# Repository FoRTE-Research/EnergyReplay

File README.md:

## Overview

This is a hardware system for replaying arbitrary energy harvesting traces to drive experimentation
on batteryless systems. It does so by measuring the voltage at the load and the current across a shunt
resistor to determine instantaneous power input into the load and comparing this actual power input to
a desired time-varying setpoint; if the actual power is below (above) the setpoint, it increases
(decreases) supply voltage produced by a DAC to approach the setpoint. Since this is all done in
software, you are free to implement whatever arbitrary functions may affect the power in your imagined
system - IV curves for a solar panel, voltage-dependent efficiencies for a converter/regulator, etc.

#### Project Status

V1.2 is available as part of this Github repo, but the PCBs have not been ordered. The only difference
between V1.1 and V1.2 is the addition of the voltage divider (R18 and R19) to reduce measured load
voltage. Because V1.1 measures load voltage directly, it cannot produce a load voltage higher than
~3.3V (software will stop voltage from increasing further if load voltage approaches this point to
avoid damaging the hardware).

An assembled and validated PCB for V1.1 is available in the lab.

## Hardware

Schematic and PCB designs are generated in KiCad version 9.

The central microcontroller is an MSP430FR5994, which drives an MCP4725 12-bit DAC. Both the MSP430 and
DAC operate at 3.3V; the output of the DAC is fed into an amplifier to increase its dynamic range to 5V.
Current flows across a 0.5 ohm shunt resistor through an optional diode and into the load. Load current
is measured by taking the voltage across the shunt resistor using a 150x differential amplifier into one
ADC pin of the MSP430. Load voltage is divided by 2 using a resistive voltage divider and fed into
another ADC pin of the MSP430. The short-circuit current of the OPA2837 op amps used is roughly 50 mA,
so at 5V the nominal maximum output power is about 250 mW.

LEDs and switches are available for basic debugging and interactive use.

#### Jumpers

**J1:** Debug header for programming the MSP430FR5994.

**J2:** Power select jumper for replay system. The center pin is connected to the system supply voltage;
it can draw power either from the debug header or from the 3V3 pin on J5.

**J3/J4:** Jumpers to connect and disconnect the green and red LEDs.

**J5:** GPIO breakout header. Also provides access to ground and 3V3 pins for supplying the system from
a non-debugger source.

**J6:** Jumper for optional diode use. RAW is connected to the load side of the shunt resistor and can
be connected to the load if the diode is not desired. Closing this jumper connects the load side of the
shunt resistor to an LM66100 ideal diode to prevent current backflow from the load. When J6 is closed,
the load should be connected on the OUT pin of J7.

**J7:** Jumper providing access to output pin for connecting load and ground pin for convenience. Do not
close this jumper.

## Software

Code is generated as a Code Composer Studio version 11 project.

The energy trace to replay is defined in the [dac.h](Code/dac.h) file as a `const float powerArray[]`
containing the setpoints and a `#define TIMESTEP` macro to set the time (in milliseconds) that power
should stay at each setpoint. This timestep is used to calculate a period value for a hardware timer
that tracks the time spent at each setpoint; when the timer rolls over, the setpoint increments.

The main application loop reads samples from the shunt and load ADC pins, converts those readings to
an actual power measurement, and compares them to the desired setpoint. The output voltage is
incremented/decremented by 1 on each iteration of the main loop; this is basically a PID controller
with K<sub>P</sub> = 1 and K<sub>I</sub> = K<sub>D</sub> = 0. Improving the design of this control
loop is one avenue for improvement in future iterations, although it currently works "well enough".
ADC, timer, and software control are all decoupled - increasing software execution speed (e.g., by
doing the actual power calculation in hardware using some clever op-amp circuits) should only have
the effect of reducing the response time of the control loop and not mess with the timing of the
power trace. If you do significantly increase the software execution speed, you should double check
that the ADC measurements are blocking so that it doesn't overshoot based on stale power readings.

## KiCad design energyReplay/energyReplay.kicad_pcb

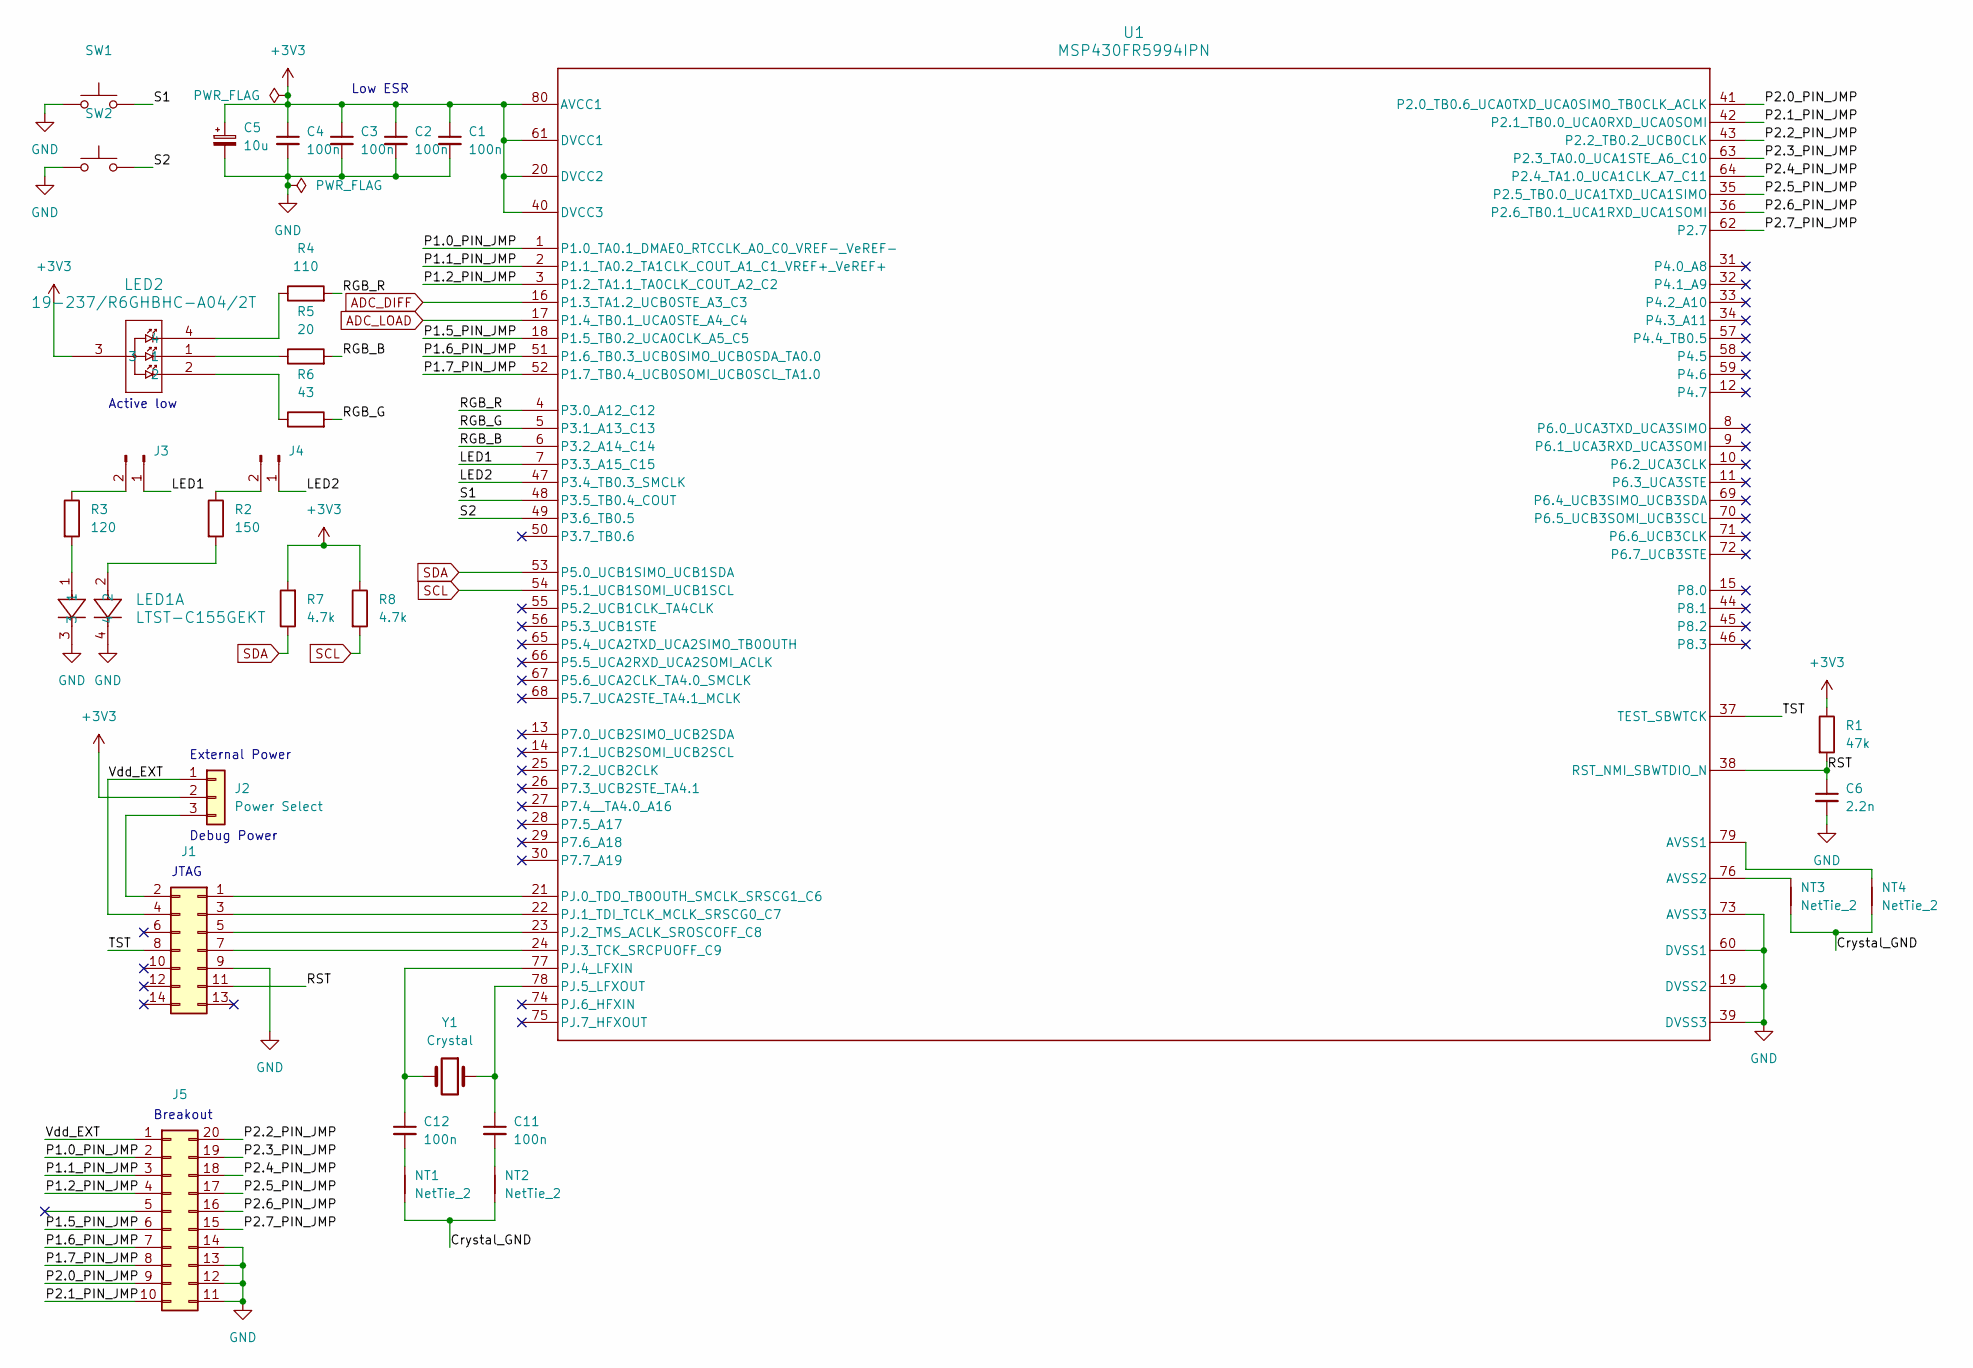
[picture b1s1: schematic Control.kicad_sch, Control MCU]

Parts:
C1, C2, C3, C4, C11, C12: 100n; C_1206_3216Metric
C5: 10u; C_1206_3216Metric
C6: 2.2n; C_1206_3216Metric
J1: Conn_02x07_Odd_Even; PinHeader_2x07_P2.54mm_Vertical
J2: Power Select; PinHeader_1x03_P2.54mm_Vertical
J3, J4: Conn_01x02_Pin; PinHeader_1x02_P2.54mm_Vertical
J5: Conn_02x10_Counter_Clockwise; PinHeader_2x10_P2.54mm_Vertical
LED1: LTST-C155GEKT; DIODE_LTST-C155GEKT_LTO
LED2: 19-237/R6GHBHC-A04/2T; EAST1616RGB_SMD_B_EVE
NT1, NT2, NT3, NT4: NetTie_2; NetTie-2_SMD_Pad0.2mm
R1: 47k; R_1206_3216Metric
R2: 150; R_1206_3216Metric
R3: 120; R_1206_3216Metric
R4: 110; R_1206_3216Metric
R5: 20; R_1206_3216Metric
R6: 43; R_1206_3216Metric
R7, R8: 4.7k; R_1206_3216Metric
SW1, SW2: SW_Push; SW_TL59NF160Q
U1: MSP430FR5994IPN; PN0080A_N
Y1: Crystal; XTAL_MS1V-T1K-32.768KHZ-12.5PF-20PPM-TA-QC

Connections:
+3V3: C1.1, C2.1, C3.1, C4.1, C5.1, J2.2, LED2.3, R1.1, R7.2, R8.1, U1.20 (DVCC2), U1.40 (DVCC3), U1.61 (DVCC1), U1.80 (AVCC1); also elsewhere on the board
/Control/Crystal_GND: NT1.1, NT2.1, NT3.1, NT4.1
/Control/LED1: J3.1, U1.7 (P3.3_A15_C15)
/Control/LED2: J4.1, U1.47 (P3.4_TB0.3_SMCLK)
/Control/P1.0_PIN_JMP: J5.2, U1.1 (P1.0_TA0.1_DMAE0_RTCCLK_A0_C0_VREF-_VeR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)
/Control/P1.1_PIN_JMP: J5.3, U1.2 (P1.1_TA0.2_TA1CLK_COUT_A1_C1_VREF+_VeRE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)
/Control/P1.2_PIN_JMP: J5.4, U1.3 (P1.2_TA1.1_TA0CLK_COUT_A2_C2)
/Control/P1.5_PIN_JMP: J5.6, U1.18 (P1.5_TB0.2_UCA0CLK_A5_C5)
/Control/P1.6_PIN_JMP: J5.7, U1.51 (P1.6_TB0.3_UCB0SIMO_UCB0SDA_TA0.0)
/Control/P1.7_PIN_JMP: J5.8, U1.52 (P1.7_TB0.4_UCB0SOMI_UCB0SCL_TA1.0)
/Control/P2.0_PIN_JMP: J5.9, U1.41 (P2.0_TB0.6_UCA0TXD_UCA0SIMO_TB0CLK_ACLK)
/Control/P2.1_PIN_JMP: J5.10, U1.42 (P2.1_TB0.0_UCA0RXD_UCA0SOMI)
/Control/P2.2_PIN_JMP: J5.20, U1.43 (P2.2_TB0.2_UCB0CLK)
/Control/P2.3_PIN_JMP: J5.19, U1.63 (P2.3_TA0.0_UCA1STE_A6_C10)
/Control/P2.4_PIN_JMP: J5.18, U1.64 (P2.4_TA1.0_UCA1CLK_A7_C11)
/Control/P2.5_PIN_JMP: J5.17, U1.35 (P2.5_TB0.0_UCA1TXD_UCA1SIMO)
/Control/P2.6_PIN_JMP: J5.16, U1.36 (P2.6_TB0.1_UCA1RXD_UCA1SOMI)
/Control/P2.7_PIN_JMP: J5.15, U1.62 (P2.7)
/Control/RGB_B: R5.2, U1.6 (P3.2_A14_C14)
/Control/RGB_G: R6.2, U1.5 (P3.1_A13_C13)
/Control/RGB_R: R4.2, U1.4 (P3.0_A12_C12)
/Control/RST: C6.1, J1.11, R1.2, U1.38 (RST_NMI_SBWTDIO_N)
/Control/S1: SW1.2, U1.48 (P3.5_TB0.4_COUT)
/Control/S2: SW2.2, U1.49 (P3.6_TB0.5)
/Control/TST: J1.8, U1.37 (TEST_SBWTCK)
/Control/Vdd_EXT: J1.4, J2.1, J5.1
ADC_DIFF: U1.16 (P1.3_TA1.2_UCB0STE_A3_C3); also elsewhere on the board
ADC_LOAD: U1.17 (P1.4_TB0.1_UCA0STE_A4_C4); also elsewhere on the board
GND: C1.2, C2.2, C3.2, C4.2, C5.2, C6.2, J1.9, J5.11, J5.12, J5.13, J5.14, LED1.3, LED1.4, SW1.1, SW2.1, U1.19 (DVSS2), U1.39 (DVSS3), U1.60 (DVSS1), U1.73 (AVSS3); also elsewhere on the board
unnamed: C11.2, NT2.2
unnamed: C12.2, NT1.2
unnamed: J1.1, U1.21 (PJ.0_TDO_TB0OUTH_SMCLK_SRSCG1_C6)
unnamed: J1.2, J2.3
unnamed: J1.3, U1.22 (PJ.1_TDI_TCLK_MCLK_SRSCG0_C7)
unnamed: J1.5, U1.23 (PJ.2_TMS_ACLK_SROSCOFF_C8)
unnamed: J1.7, U1.24 (PJ.3_TCK_SRCPUOFF_C9)
unnamed: J3.2, R3.1
unnamed: J4.2, R2.1
unnamed: LED1.1, R3.2
unnamed: LED1.2, R2.2
unnamed: LED2.1, R5.1
unnamed: LED2.2, R6.1
unnamed: LED2.4, R4.1
unnamed: NT4.2, U1.79 (AVSS1)
unnamed: NT3.2, U1.76 (AVSS2)
unnamed: C12.1, U1.77 (PJ.4_LFXIN), Y1.2
unnamed: C11.1, U1.78 (PJ.5_LFXOUT), Y1.1
SCL: R8.2, U1.54 (P5.1_UCB1SOMI_UCB1SCL); also elsewhere on the board
SDA: R7.1, U1.53 (P5.0_UCB1SIMO_UCB1SDA); also elsewhere on the board

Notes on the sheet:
JTAG
Debug Power
Active low
Breakout
Low ESR
External Power

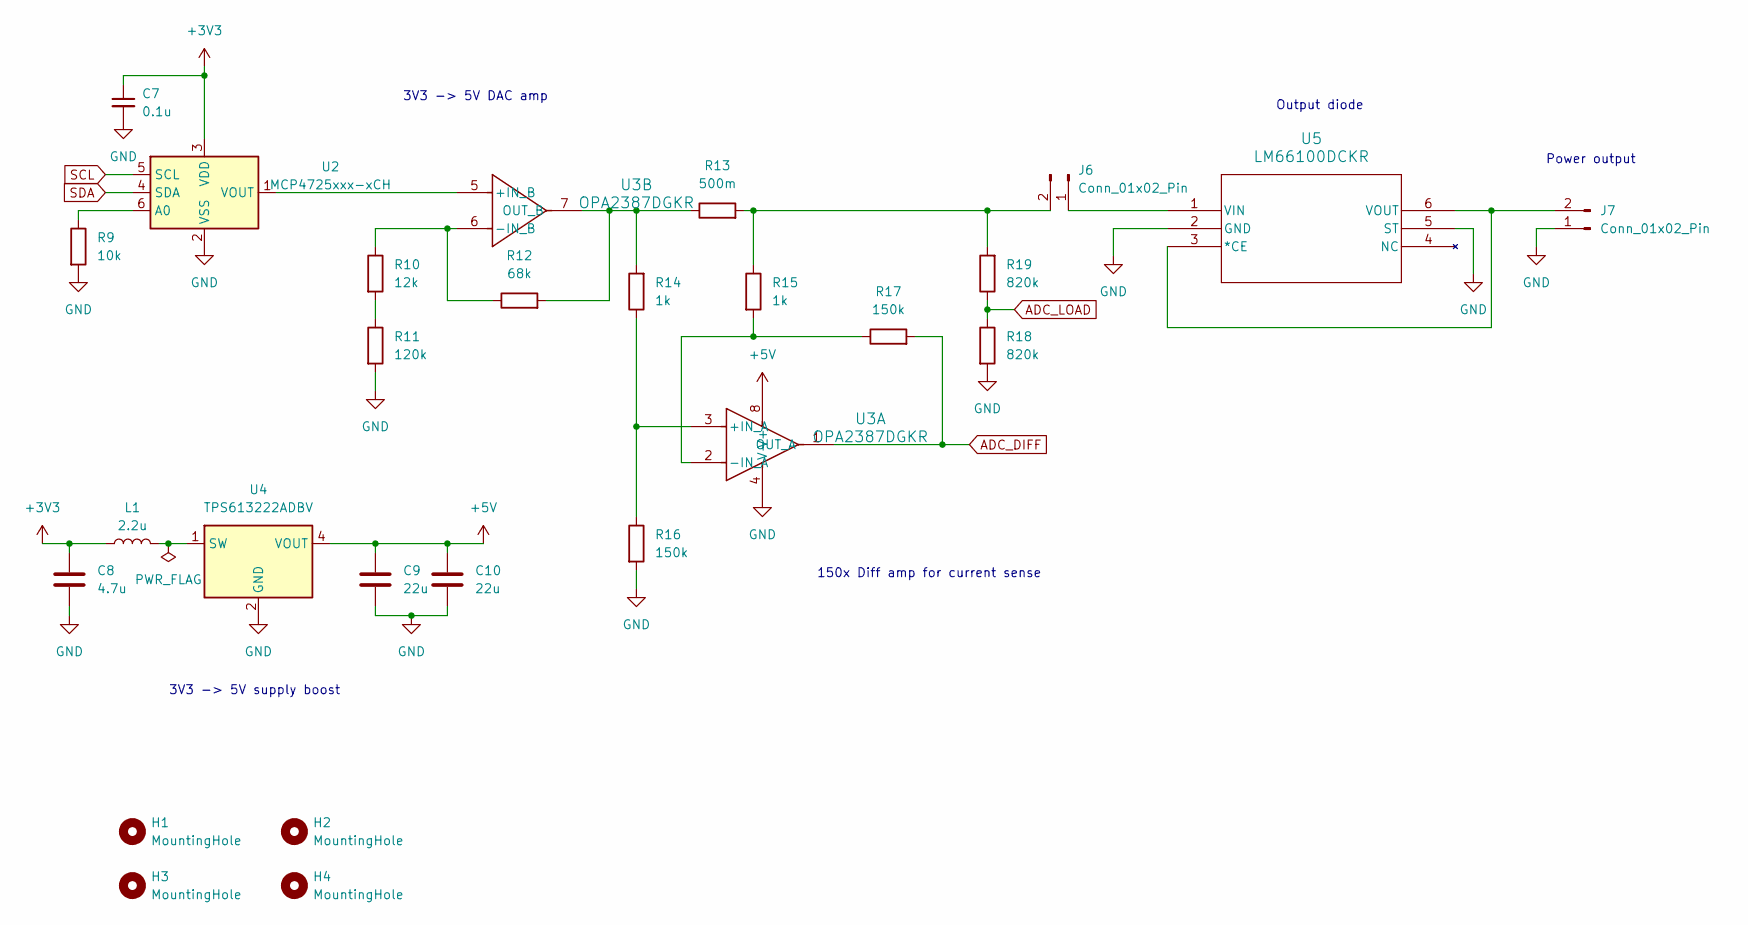
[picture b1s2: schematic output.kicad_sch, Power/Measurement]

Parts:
C7: 0.1u; C_1206_3216Metric
C8: 4.7u; C_1206_3216Metric
C9, C10: 22u; C_1206_3216Metric
H1, H2, H3, H4: MountingHole; MountingHole_3.2mm_M3
J6, J7: Conn_01x02_Pin; PinHeader_1x02_P2.54mm_Vertical
L1: 2.2u; L_1210_3225Metric
R9: 10k; R_1206_3216Metric
R10: 12k; R_1206_3216Metric
R11: 120k; R_1206_3216Metric
R12: 68k; R_1206_3216Metric
R13: 500m; R_1206_3216Metric
R14, R15: 1k; R_1206_3216Metric
R16, R17: 150k; R_1206_3216Metric
R18, R19: 820k; R_1206_3216Metric
U2: MCP4725xxx-xCH; SOT-23-6
U3: OPA2387DGKR; DGK0008A-IPC_A
U4: TPS613222ADBV; SOT-23-5
U5: LM66100DCKR; DCK6_TEX

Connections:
+3V3: C7.1, C8.1, L1.1, U2.3 (VDD); also elsewhere on the board
+5V: C9.1, C10.1, U3.8 (V+), U4.4 (VOUT)
ADC_DIFF: R17.2, U3.1 (OUT_A); also elsewhere on the board
ADC_LOAD: R18.1, R19.1; also elsewhere on the board
GND: C7.2, C8.2, C9.2, C10.2, J7.1, R9.2, R11.2, R16.2, R18.2, U2.2 (VSS), U3.4 (V-), U4.2 (GND), U5.2 (GND), U5.5 (ST); also elsewhere on the board
unnamed: J6.1, U5.1 (VIN)
unnamed: J6.2, R13.2, R15.1, R19.2
unnamed: J7.2, U5.3 (*CE), U5.6 (VOUT)
unnamed: R10.2, R11.1
unnamed: R9.1, U2.6 (A0)
unnamed: U2.1 (VOUT), U3.5 (+IN_B)
unnamed: R14.1, R16.1, U3.3 (+IN_A)
unnamed: R15.2, R17.1, U3.2 (-IN_A)
unnamed: R10.1, R12.1, U3.6 (-IN_B)
unnamed: R12.2, R13.1, R14.2, U3.7 (OUT_B)
unnamed: L1.2, U4.1 (SW)
SCL: U2.5 (SCL); also elsewhere on the board
SDA: U2.4 (SDA); also elsewhere on the board

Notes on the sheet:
Output diode
3V3 -> 5V DAC amp
Power output
3V3 -> 5V supply boost
150x Diff amp for current sense

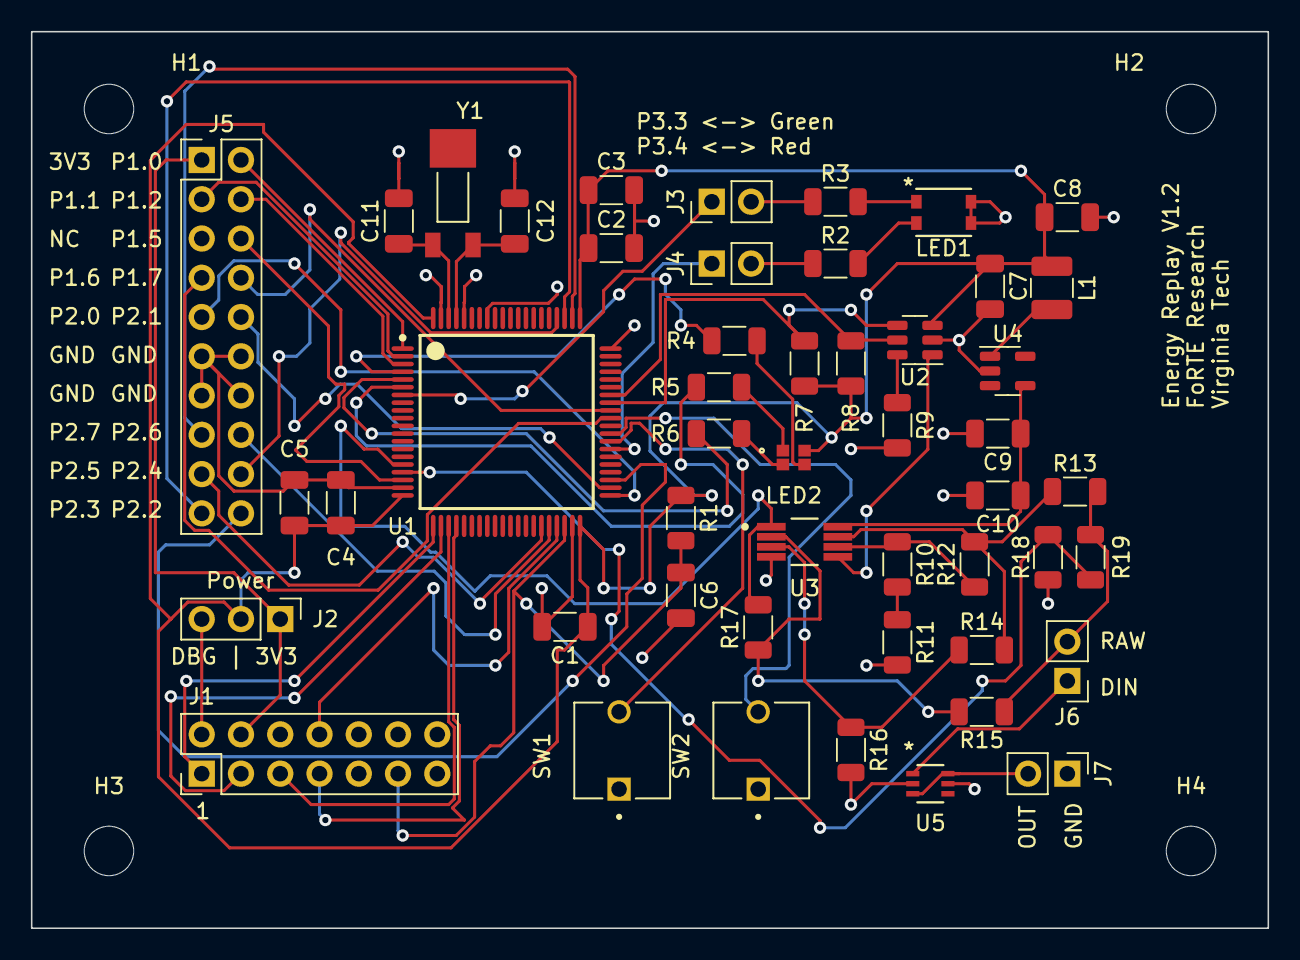
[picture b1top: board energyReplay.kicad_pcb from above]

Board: 2 copper layers, 80.0 x 58.0 mm, 57 parts (0 on the bottom side), 61 nets.

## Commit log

2024-02-28 Init
2024-05-22 Control code push
2024-09-25 1.1 KiCAD project
2025-04-21 1.2 KiCAD project and code
2025-04-29 Cleanup
2025-04-29 Test
2025-04-29 Test 2
2025-04-30 Small cleanup
2025-05-01 Upload v1.2 pcb and sch pdf
